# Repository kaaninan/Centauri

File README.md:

# Centauri
Using a friendly robot with portable EEG headset on Robot Operating System (ROS) for facilitating the lives of paralyzed people

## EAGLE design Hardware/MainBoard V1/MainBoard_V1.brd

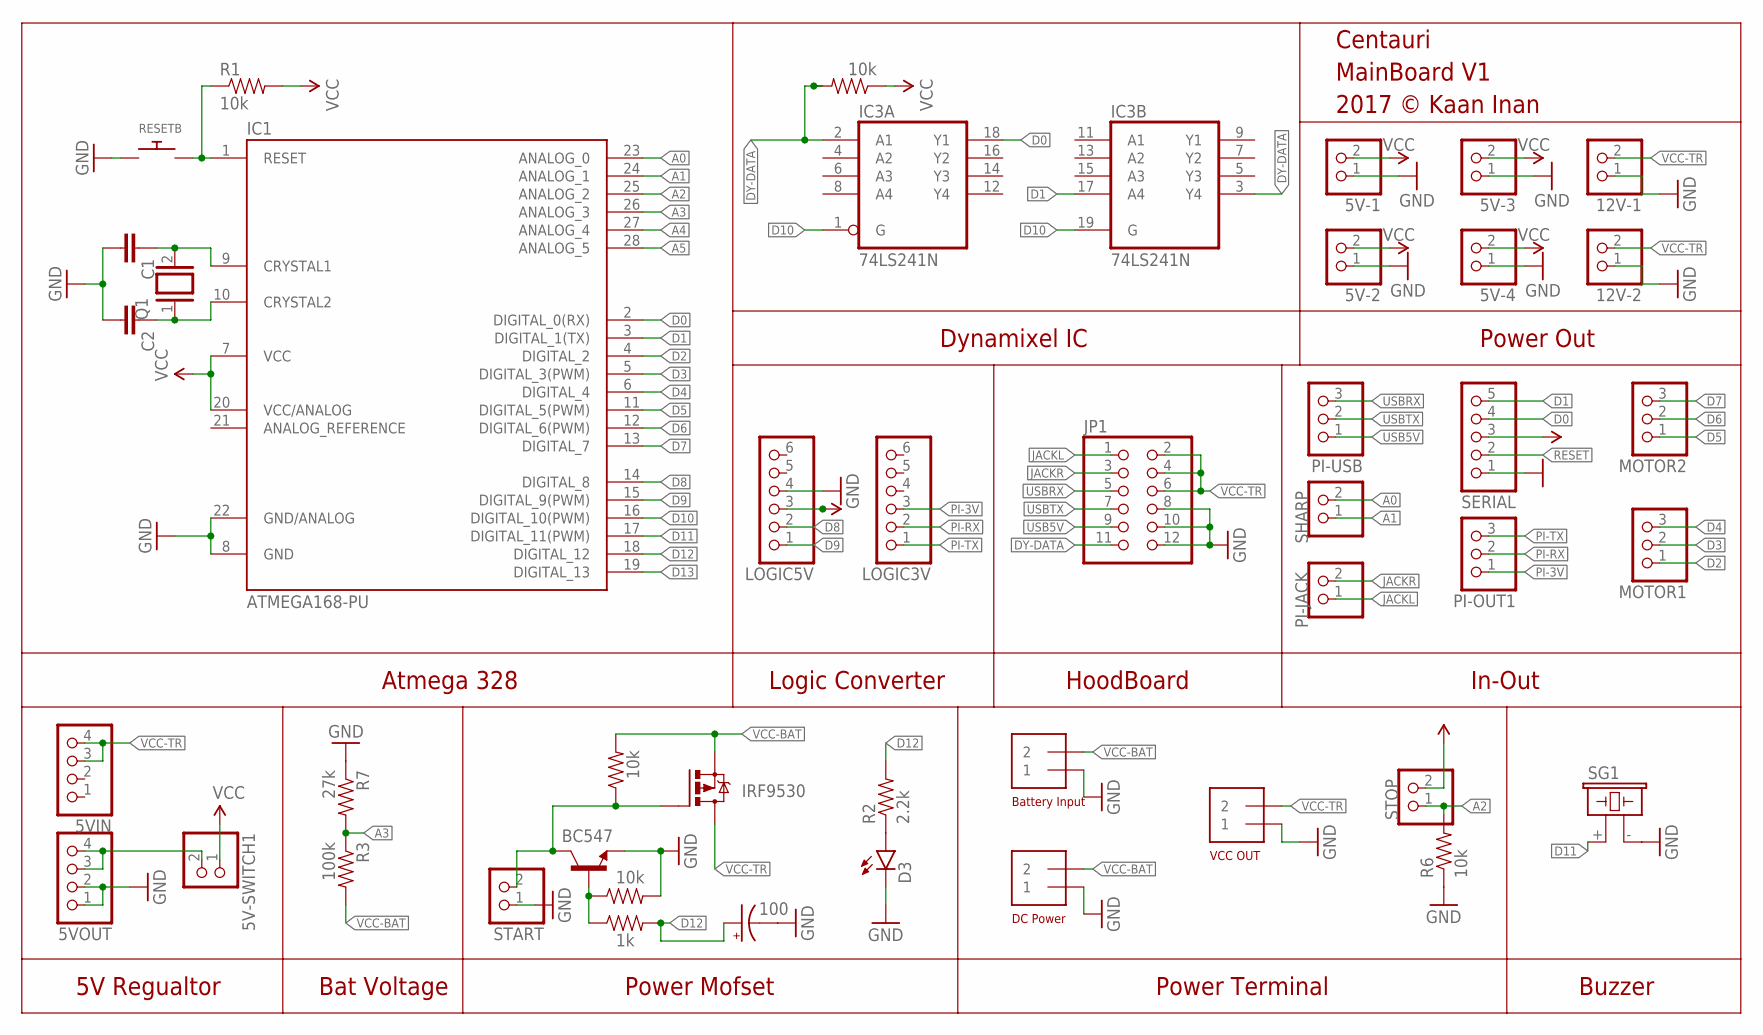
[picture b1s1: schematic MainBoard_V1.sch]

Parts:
5V-1, 5V-2, 5V-3, 5V-4, 12V-1, 12V-2: PINHD-1X2/90; 1X02/90
5V-SWITCH1: PINHD-1X2; 1X02
5VIN, 5VOUT: PINHD-1X4; 1X04
C1, C2: 0.1UF-50V-20%(PTH)KIT-EZ; CAP-PTH-SMALL-KIT
C7: 100; CPOL-RADIAL-100UF-25V
D3: LED3MM
DC1: 1X2-3.5MM
IC1: ATMEGA168-PU; DIL28-3
IC3: 74LS241N; DIL20
JP1: PINHD-2X6; 2X06
LOGIC3V, LOGIC5V: PINHD-1X6; 1X06
MOTOR1, MOTOR2: PINHD-1X3; 1X03
PI-JACK: PINHD-1X2; 1X02
PI-OUT1: PINHD-1X3; 1X03
PI-USB: PINHD-1X3; 1X03
PIL1: 1X2-3.5MM
Q1: XTAL/S; QS
Q2: IRF9530; TO220BV
Q6: BC547; TO-92
R1, R6, R8, R17, R19: 10k; AXIAL-0.3
R2: 2.2k; AXIAL-0.3
R3: 100k; AXIAL-0.3
R7: 27k; AXIAL-0.3
R20: 1k; AXIAL-0.3
RESETB: SWITCH_PUSHBUTTONEVQ-PE; TACT_PANA-EVQ
SERIAL: PINHD-1X5; 1X05
SG1: F/CM12P
SHARP: PINHD-1X2; 1X02
START: PINHD-1X2; 1X02
STOP: PINHD-1X2; 1X02
VCC1: 1X2-3.5MM

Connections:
A0: IC1.23 (ANALOG_0), SHARP.2
A1: IC1.24 (ANALOG_1), SHARP.1
A2: IC1.25 (ANALOG_2), R6.P$2 (2), STOP.1
A3: IC1.26 (ANALOG_3), R3.P$1 (1), R7.P$2 (2)
A4: IC1.27 (ANALOG_4)
A5: IC1.28 (ANALOG_5)
D0: IC1.2 (DIGITAL_0(RX)), IC3.18 (Y1), SERIAL.4
D1: IC1.3 (DIGITAL_1(TX)), IC3.17 (A4), SERIAL.5
D2: IC1.4 (DIGITAL_2), MOTOR1.1
D3: IC1.5 (DIGITAL_3(PWM)), MOTOR1.2
D4: IC1.6 (DIGITAL_4), MOTOR1.3
D5: IC1.11 (DIGITAL_5(PWM)), MOTOR2.1
D6: IC1.12 (DIGITAL_6(PWM)), MOTOR2.2
D7: IC1.13 (DIGITAL_7), MOTOR2.3
D8: IC1.14 (DIGITAL_8), LOGIC5V.2
D9: IC1.15 (DIGITAL_9(PWM)), LOGIC5V.1
D10: IC1.16 (DIGITAL_10(PWM)), IC3.1 (G), IC3.19 (G)
D11: IC1.17 (DIGITAL_11(PWM)), SG1.+ (1)
D12: C7.1 (+), IC1.18 (DIGITAL_12), R2.P$2 (2), R20.P$2 (2)
D13: IC1.19 (DIGITAL_13)
DY-DATA: IC3.2 (A1), IC3.3 (Y4), JP1.11, R8.P$2 (2)
GND: 5V-1.1, 5V-2.1, 5V-3.1, 5V-4.1, 5VOUT.1, 5VOUT.2, 12V-1.1, 12V-2.1, C1.2, C2.2, C7.2 (-), D3.K (C), DC1.1, IC1.8 (GND), IC1.22 (GND/ANALOG), IC3.10 (GND), JP1.8, JP1.10, JP1.12, LOGIC5V.4, PIL1.1, Q6.3 (E), R6.P$1 (1), R7.P$1 (1), R19.P$2 (2), RESETB.P$1, SERIAL.1, SG1.- (2), START.1, VCC1.1
JACKL: JP1.1, PI-JACK.1
JACKR: JP1.3, PI-JACK.2
unnamed: C1.1, IC1.9 (CRYSTAL1), Q1.2
unnamed: C2.1, IC1.10 (CRYSTAL2), Q1.1
unnamed: D3.A, R2.P$1 (1)
unnamed: 5V-SWITCH1.2, 5VOUT.3, 5VOUT.4
unnamed: Q2.G, Q6.1 (C), R17.P$1 (1), START.2
unnamed: Q6.2 (B), R19.P$1 (1), R20.P$1 (1)
PI-3V: LOGIC3V.3, PI-OUT1.1
PI-RX: LOGIC3V.2, PI-OUT1.2
PI-TX: LOGIC3V.1, PI-OUT1.3
RESET: IC1.1 (RESET), R1.P$1 (1), RESETB.P$2, SERIAL.2
USB5V: JP1.9, PI-USB.1
USBRX: JP1.5, PI-USB.3
USBTX: JP1.7, PI-USB.2
VCC: 5V-1.2, 5V-2.2, 5V-3.2, 5V-4.2, 5V-SWITCH1.1, IC1.7 (VCC), IC1.20 (VCC/ANALOG), IC3.20 (VCC), LOGIC5V.3, R1.P$2 (2), R8.P$1 (1), SERIAL.3, STOP.2
VCC-BAT: DC1.2, PIL1.2, Q2.S, R3.P$2 (2), R17.P$2 (2)
VCC-TR: 5VIN.3, 5VIN.4, 12V-1.2, 12V-2.2, JP1.2, JP1.4, JP1.6, Q2.D, VCC1.2

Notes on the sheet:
Atmega 328
5V Regualtor
Power Out
Dynamixel IC
Bat Voltage
Power Terminal
In-Out
Battery Input
DC Power
VCC OUT
Power Mofset
Centauri MainBoard V1 2017 © Kaan Inan
Logic Converter
Buzzer
HoodBoard

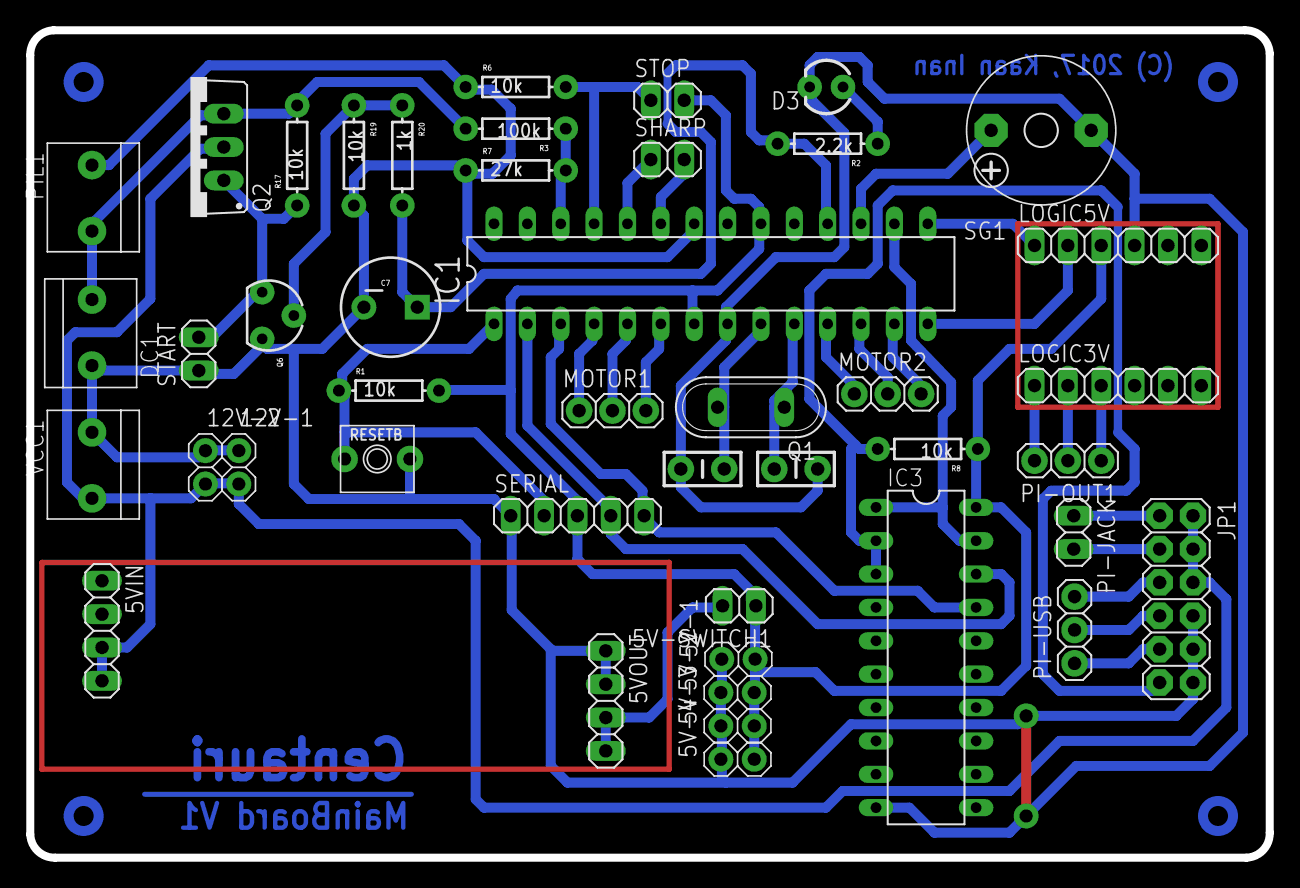
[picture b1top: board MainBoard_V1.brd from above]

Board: 2 copper layers, 94.4 x 63.0 mm, 44 parts (0 on the bottom side), 37 nets.

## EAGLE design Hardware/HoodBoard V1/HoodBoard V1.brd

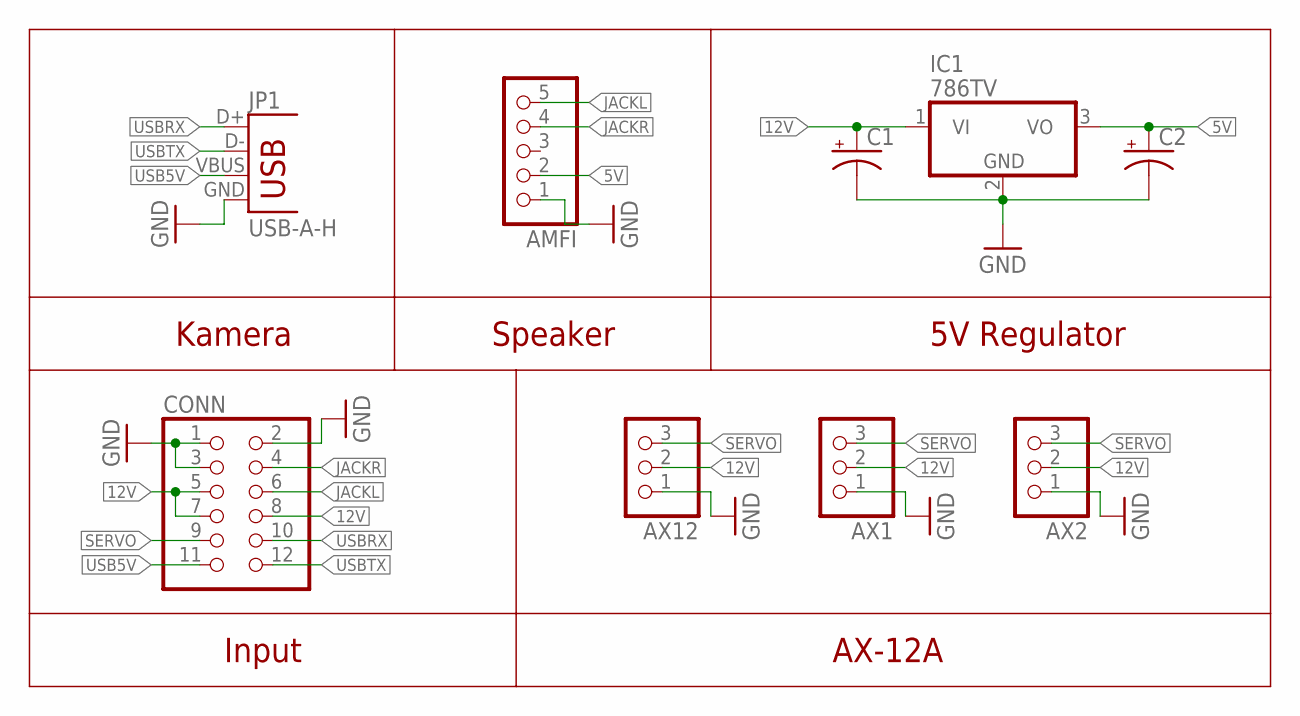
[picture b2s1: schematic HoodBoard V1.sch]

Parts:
AMFI: PINHD-1X5; 1X05
AX1, AX2, AX12: PINHD-1X3; 1X03
C1, C2: 10UF-25V-20%(PTH); CPOL-RADIAL-10UF-25V
CONN: PINHD-2X6; 2X06
IC1: 786TV; TO220V
JP1: USB-A-H

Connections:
5V: AMFI.2, C2.1 (+), IC1.3 (VO)
12V: AX1.2, AX2.2, AX12.2, C1.1 (+), CONN.5, CONN.7, CONN.8, IC1.1 (VI)
GND: AMFI.1, AX1.1, AX2.1, AX12.1, C1.2 (-), C2.2 (-), CONN.1, CONN.2, CONN.3, IC1.2 (GND), JP1.GND
JACKL: AMFI.5, CONN.6
JACKR: AMFI.4, CONN.4
SERVO: AX1.3, AX2.3, AX12.3, CONN.9
USB5V: CONN.11, JP1.VBUS
USBRX: CONN.10, JP1.D+
USBTX: CONN.12, JP1.D-

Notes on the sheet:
Kamera
Speaker
5V Regulator
AX-12A
Input

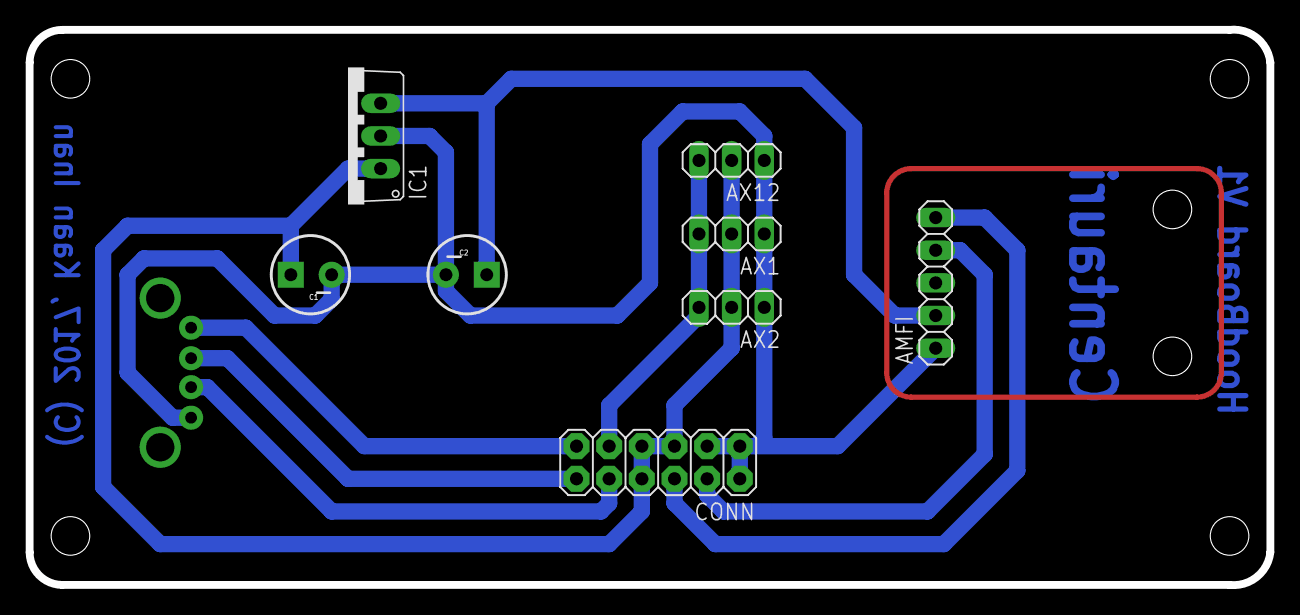
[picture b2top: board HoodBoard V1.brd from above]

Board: 2 copper layers, 96.5 x 43.2 mm, 9 parts (1 on the bottom side), 9 nets.

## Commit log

2017-04-11 initial
2017-04-11 ros packages
2017-04-11 catkin update
2017-04-11 ignore files
2017-04-11 ignore
2017-04-11 .gitignore is now working
2017-04-13 serial connection added
2017-04-13 packages added
2017-04-15 serial completed, directory updated
2017-04-15 .gitignore update
2017-04-23 up to date
2017-04-24 eeg update
2017-04-29 sound is okey
2017-04-29 update stop button func
2017-04-29 software update
2017-04-29 hardware reset added
2017-04-29 hardware serial bug fix
2017-04-29 dis warning added
2017-05-08 web added
2017-05-12 last update

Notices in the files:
Hardware/HoodBoard V1/HoodBoard V1.brd:
(C) 2017, Kaan Inan
parts and their libraries:
SparkFun-Connectors: Licensing: Creative Commons ShareAlike 4.0 International - https://creativecommons.org/licenses/by-sa/4.0
